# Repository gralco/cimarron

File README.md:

# Cimarron 3D Printer Electronics

## Chipset

Octavo Systems/TI OSD335x

## Other ICs Being Used

Trinamic TMC2130 Stepper Driver

EMMC**G-S100 Embedded MMC

## Operating System

Embedded ARM GNU/Linux Kamikaze

## Bootloader

DAS U-Boot

## Control Software

Potential software to run on Cimarron:

 - [Redeem](https://bitbucket.org/intelligentagent/redeem)
 - [MachineKit](https://github.com/machinekit/machinekit)
 - [Unicorn](https://github.com/fastbot3d/firmware)
 - [Ember-Firmware](https://github.com/spark3dp/ember-firmware)

## Credits

Works that Cimarron is based off of includes:

 - Thing Printer Replicape Rev B3
 - BeagleBone Black Wireless (minus the WL1835 chip)
 - PocketBone
 - BeagleBone Black
 - Tinkerforge Silent Stepper Brick
 - Trinamic TMC-260 Shield

## License

Cimarron is published under [CC-BY-SA 4.0](COPYING.md).

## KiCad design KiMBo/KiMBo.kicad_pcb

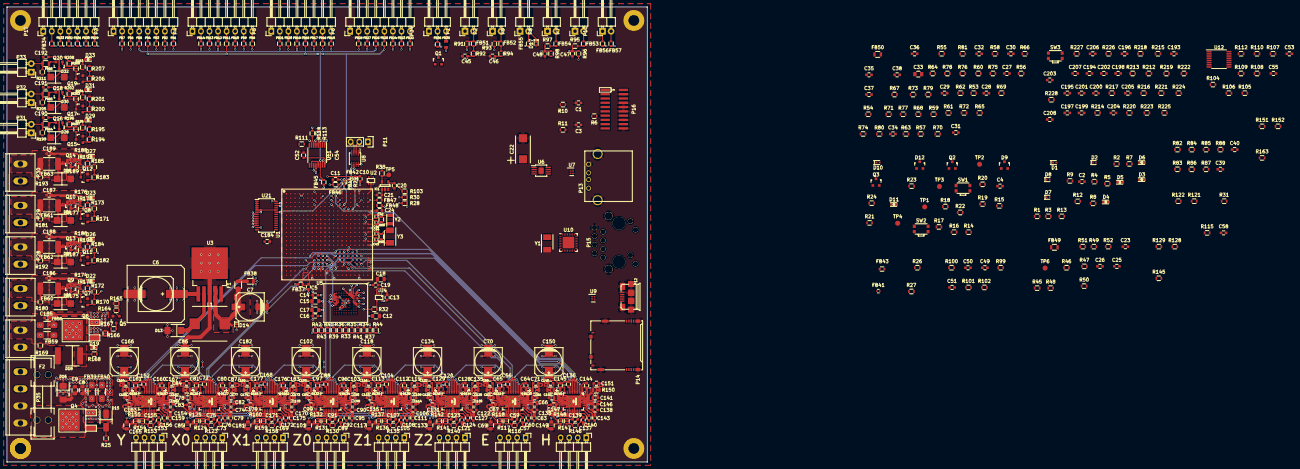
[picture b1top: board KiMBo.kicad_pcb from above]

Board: 6 copper layers, 190.0 x 135.0 mm, 628 parts (0 on the bottom side), 443 nets.

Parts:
C1, C3, C5, C10, C11, C13, C14, C16, C19, C20, C21, C23, C24, C25, C26, C29, C30, C31, C49, C50, C51, C52, C53, C54, C55, C56, C58, C63, C66, C67, C68, C71, C72, C74, C79, C82, C83, C84, C87, C88, C90, C95, C98, C99, C100, C103, C104, C106, C111, C114, C115, C116, C119, C120, C122, C127, C130, C131, C132, C135, C136, C138, C138#2, C143, C146, C147, C148, C151, C152, C154, C159, C162, C163, C164, C167, C168, C170, C175, C178, C179, C180, C183, C184: 100nF; C_0603
C2, C60, C76, C92, C108, C124, C140, C156, C172: 22nF; C_0603
C4: 2.2μF; C_0603
C6: 470μF; c_elec_16x16.5
C7: 220μF; c_elec_8x10.2
C8, C9: 22μF; C_0805
C12, C15, C17: 2.2μF; C_0805
C18: 4.7μF; C_0805
C22: 220μF; TantalC_SizeD_EIA-7343_Reflow
C27, C28: 30pF; C_0603
C32, C61, C62, C64, C65, C77, C78, C80, C81, C93, C94, C96, C97, C109, C110, C112, C113, C125, C126, C128, C129, C141, C142, C144, C145, C157, C158, C160, C161, C173, C174, C176, C177: 470pF; C_0603
C33, C69, C85, C101, C117, C133, C149, C165, C181: 10μF; C_0805
C34: 1μF; C_0603
C35, C36, C37, C38: DNP-15pF; C_0603
C39, C40: 10μF; C_0603
C41, C42, C43, C44: 18pF; Crystal_C_0402
C45, C46, C59, C75, C91, C107, C123, C139, C155, C171: 4.7μF; C_0603
C47, C48: 39nF; C_0603
C57, C73, C89, C105, C121, C137, C153, C169: 470nF; C_0603
C70, C86, C102, C118, C134, C150, C166, C182: 100μF; c_elec_8x10
C185, C186, C187, C188, C189, C190, C191, C192: 4.7nF; C_0603
C193, C194, C195, C196, C197, C198, C199, C200, C201, C202, C203, C204, C205, C206, C207, C208: 47pF; C_0603
D1, D10, D17: TPD1E04U04DPYR; TPD_PX1SON
D2, D7, D8, D14: D5V0F1U2S9; SOD-923
D3, D4, D5, D6, D11, D19, D22, D23, D26, D27, D29, D31, D33: LED; LED_0603
D9: TLVH431; SOT-23
D12: DNP-TLVH431; SOT-23
D13: SK54A-LTP; SK-DO-214AC
D15: SMAZ10; SMA-DO-214AC
D16: SMAJ26A; SK-DO-214AC
D18: SK1545-TP; SK-DO-214AB
D20, D21, D24, D25, D28, D30, D32: MBRA340T3; MBR-DO-214AC
F1: PTC; PTC_SMD0805_Reflow
F2: 0891020.NXS; 3557-2-Fuseholder
FB1, FB2, FB8, FB9, FB15, FB16, FB22, FB23, FB29, FB37: MPZ1608S102ATA00; Ferrite_Bead_0603
FB3, FB4, FB5, FB6, FB7, FB10, FB11, FB12, FB13, FB14, FB17, FB18, FB19, FB20, FB21, FB24, FB25, FB26, FB27, FB28, FB30, FB31, FB32, FB33, FB34, FB36, FB42, FB43, FB45, FB46, FB47, FB48, FB51, FB52, FB53, FB54, FB55, FB56, FB57: MMZ1608A252BTA00; Ferrite_Bead_0603
FB35, FB38: MPZ2012S601AT000; Ferrite_Bead_0805
FB39, FB40, FB58, FB59: BLM31SN500SN1L; R_1206_HandSoldering
FB41, FB44: BLM15AG102SN1D; R_0402
FB49, FB50: LI0805H151R-10; R_0805
FB60, FB61, FB62, FB63: FBMH4532HM132-T; Ferrite_Bead_1812
FB64, FB65, FB66: CIM21J202NE; R_0805
IC1: 24LC32AT-I/OT; SOT-23-5
L1: 47μH; IHLP_Inductor
P1: BED_THERM; Pin_Header_Angled_1x02
P2: ADC; Pin_Header_Angled_1x02
P3: TOOLHEAD0; Pin_Header_Angled_1x08
P4: TOOLHEAD1; Pin_Header_Angled_1x08
P5: DOCK0; Pin_Header_Angled_1x08
P6: DOCK1; Pin_Header_Angled_1x08
P7: X1; Pin_Header_Angled_1x02
P8: Y1; Pin_Header_Angled_1x02
P9: Z1; Pin_Header_Angled_1x02
P10: ENC; Pin_Header_Angled_1x02
P11: Serial; Pin_Header_Straight_1x03
P12: μUSB; USB_MICRO_B_ST-USB-001E
P13: USB_Type_A; USB_A
P14: μSD; SCHA5B0200
P15: Ethernet; Ethernet-LPJ0011BBNL
P16: JTAG
P17: LCD; Pin_Header_Angled_1x07
P18: E_MOTOR; Pin_Header_Angled_1x04
P19: H_MOTOR; Pin_Header_Angled_1x04
P20: X0_MOTOR; Pin_Header_Angled_1x04
P21: X1_MOTOR; Pin_Header_Angled_1x04
P22: Y_MOTOR; Pin_Header_Angled_1x04
P23: Z0_MOTOR; Pin_Header_Angled_1x04
P24: Z1_MOTOR; Pin_Header_Angled_1x04
P25: Z2_MOTOR; Pin_Header_Angled_1x04
P26: BED_HEAT; euro_header_2_angled
P27: E_HEAT; euro_header_2_angled
P28: H_HEAT; euro_header_2_angled
P29: DOCK0_HEAT; euro_header_2_angled
P30: DOCK1_HEAT; euro_header_2_angled
P31: E_FAN; Pin_Header_Angled_1x02
P32: H_FAN; Pin_Header_Angled_1x02
P33: CASE_FAN; Pin_Header_Angled_1x02
P34: PWM; Pin_Header_Angled_1x03
P35: PWR_Input; euro_header_4_angled
Q1, Q5, Q7, Q8, Q11, Q12, Q15, Q17, Q19: 2N7002; SOT-23
Q2: MMBT2907; SOT-23
Q3: DNP-MMBT2907; SOT-23
Q4, Q6: IPD90P03P4-04; TO-252-2Lead
Q9, Q10, Q13, Q14, Q16, Q18, Q20: DMP3098L-7; SOT-23
R1, R2, R3, R4: 1kΩ; R_0603
R5, R8: 470Ω; R_0603
R6, R10, R11, R20, R26, R27, R118, R125, R132, R137, R142, R148, R155, R160: 4.75kΩ; R_0603
R7, R14, R15, R18, R33, R34, R35, R36, R37, R38, R39, R40, R41, R42, R43, R44, R47, R71, R73, R75, R77, R78, R82, R83, R84, R85, R86, R87, R88, R92, R94, R168, R169, R178, R179, R180, R181, R190, R191, R192, R193, R198, R199, R204, R205, R210, R211: 10kΩ; R_0603
R9, R28, R29, R30, R31, R32, R45, R49, R51, R66: 0Ω; R_0603
R12, R13, R91, R93, R96, R98, R100, R101, R102, R103, R104, R105, R106, R107, R108, R109, R110, R111, R112, R113, R114, R115, R121, R122, R128, R129, R145, R151, R152, R163, R165, R166, R167, R172, R173, R174, R175, R176, R177, R184, R185, R186, R187, R188, R189, R195, R196, R197, R201, R202, R203, R207, R208, R209: 4.7kΩ; R_0603
R16: 499Ω; R_0603
R17, R22: DNPΩ; R_0603
R19: 40.2kΩ; R_0603
R21: DNP-499Ω; R_0603
R23: DNP-10kΩ; R_0603
R24: DNP-40.2kΩ; R_0603
R25, R52, R212, R214, R215, R216, R217, R218, R219, R220, R221, R222, R223, R224, R225, R226, R227, R228: 100kΩ; R_0603
R46, R48, R68, R79, R80, R81: 1.5kΩ; R_0603
R50: 100mΩ; R_0603
R53, R164, R170, R171, R182, R183, R194, R200, R206: 10Ω; R_0603
R54, R89: DNP-1MΩ; R_0603
R55: DNP-10Ω; R_0603
R56, R57, R58, R59, R60, R61, R62, R63, R64, R65, R95, R97, R99, R213: 100Ω; R_0603
R67: DNP-0Ω; R_0603
R69, R72, R74, R76: 49.9Ω; R_0603
R70: 12.1kΩ; R_0603
R90: 1MΩ; R_0603
R116, R123, R130, R135, R140, R146, R153, R158: 2.2Ω; R_0603
R117, R124, R131, R136, R141, R147, R154, R159: 5.23kΩ; R_0603
R119, R120, R126, R127, R133, R134, R138, R139, R143, R144, R149, R150, R156, R157, R161, R162: 220mΩ; R_0805
SW1: RESET; KMR_SW_SPST_EVQP7A
SW2: Power; KMR_SW_SPST_EVQP7A
SW3: μSD_Boot; KMR_SW_SPST_EVQP7A
TP1, TP2, TP3, TP4, TP5, TP6: Test_Point; Measurement_Point_Round-SMD-Pad_Small
U1: OSD3358; BGA-400-1-27mm
U2, U4: 74LVC1G06; SC-70-5
U3: LM2592HVSX-5.0; TO-263-5Lead
U5: EMMC**G-S100; EMMCxxG-S100
U6: TPS2051B; DGN-MSOP-8_3x3mm_Pitch0.65mm
U7, U9: TPD4S012; DRY-DFN-6-1EP_2x2mm_Pitch0.5mm
U8: 74LVC2G241; DCT-MSOP-8_3x3mm_Pitch0.65mm
U10: LAN8710A; QFN-32-1EP_5x5mm_Pitch0.5mm
U11, U12: 74HC595; TSSOP-16_4.4x5mm_Pitch0.65mm
U13, U14, U15, U16, U17, U18, U19, U20: TMC2130; QFN36_5X6
U21: PCA9685; TSSOP-28_4.4x9.7mm_Pitch0.65mm
Y1: 7A-25.000MAAJ-T; Crystal_SMD_7A_2Pads
Y2: AH-32.768KDZY-T; Crystal_SMD_32.768kHz_2Pads
Y3: 7A-24.000MAAJ-T; Crystal_SMD_7A_2Pads

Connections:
+24V: C6.1, C8.1, C9.1, C58.2, C63.1, C66.1, C67.1, C69.1, C70.1, C74.2, C79.1, C82.1, C83.1, C85.1, C86.1, C90.2, C95.1, C98.1, C99.1, C101.1, C102.1, C106.2, C111.1, C114.1, C115.1, C117.1, C118.1, C122.2, C127.1, C130.1, C131.1, C133.1, C134.1, C138.2, C138#2.2, C143.1, C146.1, C147.1, C149.1, C150.1, C154.2, C159.1, C162.1, C163.1, C165.1, C166.1, C170.2, C175.1, C178.1, C179.1, C181.1, C182.1, C185.1, C186.1, C187.1, C188.1, C189.1, C190.1, C191.1, C192.1, D16.1, FB39.2, FB40.2, Q6.3, Q9.3, Q10.3, Q13.3, Q14.3, Q16.3, Q18.3, Q20.3, R166.1, R174.1, R176.1, R186.1, R188.1, R196.1, R202.1, R208.1, U3.1, U13.16, U13.30, U13.31, U14.16, U14.30, U14.31, U15.16, U15.30, U15.31, U16.16, U16.30, U16.31, U17.16, U17.30, U17.31, U18.16, U18.30, U18.31, U19.16, U19.30, U19.31, U20.16, U20.30, U20.31
/ADC: C46.2, R94.2, U1.C8
/BED_THERM: C45.2, R92.2, U1.A8
/CLKOUT2: FB44.1, P16.18, R29.1, R163.2, U21.23
/Configuration/LCD.D0.B0--B3: C208.1, R212.1, U1.R1
/Configuration/LCD.D1.B1--B4: C207.1, R214.1, U1.R2
/Configuration/LCD.D2.B2--B5: C206.1, R213.2, R215.2, U1.R3
/Configuration/LCD.D3.B3--B6: C205.1, R216.2, U1.R4
/Configuration/LCD.D4.B4--B7: C204.1, R217.2, U1.T1
/Configuration/LCD.D5.G0--G2: C203.1, R218.2, U1.T2
/Configuration/LCD.D6.G1--G3: C202.1, R219.1, U1.T3
/Configuration/LCD.D7.G2--G4: C201.1, R220.1, U1.T4
/Configuration/LCD.D8.G3--G5: C200.1, R221.1, U1.U1
/Configuration/LCD.D9.G4--G6: C199.1, R222.1, U1.U2
/Configuration/LCD.D10.G5--G7: C198.1, R223.1, U1.U3
/Configuration/LCD.D11.R0--R3: C197.1, R224.1, U1.U4
/Configuration/LCD.D12.R1--R4: C196.1, R225.1, U1.V2
/Configuration/LCD.D13.R2--R5: C195.1, R226.1, U1.V3
/Configuration/LCD.D14.R3--R6: C194.1, R227.2, U1.V4
/Configuration/LCD.D15.R4--R7: C193.1, R228.1, U1.T5
/ENC_A: C50.1, R31.2, R101.1
/ENC_B: C51.1, R102.1, U1.R7
/E_DIR: U1.U13, U13.7
/E_FAULT: R115.2, U1.V12, U13.20
/E_STEP: U1.U18, U13.6
/Endstops/ENC_A_IN: FB56.2, P10.1
/Endstops/ENC_B_IN: FB57.2, P10.2
/Endstops/X1_IN: FB53.2, P7.2
/Endstops/Y1_IN: FB54.2, P8.2
/Endstops/Z1_IN: D17.1, FB55.2, P9.2
/Ethernet/CRS: R65.1, U10.14
/Ethernet/ETH_TXD4: R73.1, U10.18
/Ethernet/GRNA: P15.9, U10.3
/Ethernet/MDIO_CLK: U1.M18, U10.17
/Ethernet/MDIO_DATA: R68.2, U1.M17, U10.16
/Ethernet/MII1_COL: R64.2, U1.H16
/Ethernet/MII1_CRS_DV: R65.2, U1.H17
/Ethernet/MII1_REFCLK: R55.2, R67.2, U1.H18
/Ethernet/MII1_RXCLK: R61.2, U1.L18
/Ethernet/MII1_RXD0: R59.2, U1.M16
/Ethernet/MII1_RXD1: R58.2, U1.L15
/Ethernet/MII1_RXD2: R57.2, U1.L16
/Ethernet/MII1_RXD3: R56.2, U1.L17
/Ethernet/MII1_RXDV: R60.2, U1.J17
/Ethernet/MII1_RXERR: R62.2, U1.J15
/Ethernet/MII1_TXCLK: R63.2, U1.K18
/Ethernet/MII1_TXD0: U1.K17, U10.22
/Ethernet/MII1_TXD1: U1.K16, U10.23
/Ethernet/MII1_TXD2: U1.K15, U10.24
/Ethernet/MII1_TXD3: U1.J18, U10.25
/Ethernet/MII1_TXEN: U1.J16, U10.21
/Ethernet/MODE2: R64.1, R79.2, U10.15
/Ethernet/PHY_VDDCR: C32.1, C34.1, U10.6
/Ethernet/RBIAS: R70.1, U10.32
/Ethernet/RCLKIN: R66.1, R67.1, U10.5
/Ethernet/RD+: C35.1, P15.1, R69.2, U10.31
/Ethernet/RD-: C36.1, P15.2, R72.2, U10.30
/Ethernet/REFCLKO: R55.1, R61.1, R78.1, U10.7
/Ethernet/RXD0/MODE0: R59.1, R81.2, U10.11
/Ethernet/RXD1/MODE1: R58.1, R80.2, U10.10
/Ethernet/RXD2/RMIISEL: R57.1, R77.1, U10.9
/Ethernet/RXD3/PHYAD2: R56.1, R75.1, U10.8
/Ethernet/RXDV: R60.1, U10.26
/Ethernet/RXER/PHYAD0: R62.1, R71.1, U10.13
/Ethernet/TD+: C37.1, P15.3, R74.2, U10.29
/Ethernet/TD-: C38.1, P15.6, R76.2, U10.28
/Ethernet/TXCLK: R63.1, U10.20
/Ethernet/YELA: P15.12, R7.1, U10.2
/Fans/CASE_FAN: C192.2, FB66.2, P33.2, R211.1
/Fans/CASE_FAN_IN: R206.2, R207.2, U21.6
/Fans/E_FAN: C190.2, FB64.2, P31.2, R199.1
/Fans/E_FAN_IN: R194.2, R195.2, U21.8
/Fans/H_FAN: C191.2, FB65.2, P32.2, R205.1
/Fans/H_FAN_IN: R200.2, R201.2, U21.7
/Flash/EMMC_RSTN: R32.1, R44.2, U5.K5
/Flash/GPIO1_16.SIP: R31.1, U1.R13
/Flash/MMC1_CLK: R43.2, U1.U9, U5.M6, U5.M7, U5.N8, U5.P9
/Flash/MMC1_CMD: R42.2, U1.V9, U5.M5, U5.N6, U5.N7, U5.P8
/Flash/MMC1_DAT0: R33.2, U1.U7, U5.A3
/Flash/MMC1_DAT1: R34.2, U1.V7, U5.A4
/Flash/MMC1_DAT2: R35.2, U1.R8, U5.A5
/Flash/MMC1_DAT3: R36.2, U1.T8, U5.A1, U5.B2
/Flash/MMC1_DAT4: R37.2, U1.U8, U5.A2, U5.B3
/Flash/MMC1_DAT5: R39.2, U1.V8, U5.B4, U5.C3, U5.D1, U5.D2
/Flash/MMC1_DAT6: R40.2, U1.R9, U5.B5, U5.C5, U5.D4, U5.E3, U5.F2, U5.G1
/Flash/MMC1_DAT7: R41.2, U1.T9, U5.A8, U5.B6, U5.B7
/H_DIR: U1.V13, U18.7
/H_FAULT: R145.2, U1.T7, U18.20
/H_STEP: U1.R12, U18.6
/Heaters/BED_HEAT: C185.2, FB58.2, FB59.2, P26.1, R169.1
/Heaters/BED_HEAT_IN: R164.2, R165.2, U21.13
/Heaters/DOCK0_HEAT: C187.2, FB61.2, P29.1, R181.1
/Heaters/DOCK0_HEAT_IN: R171.2, R173.2, U21.10
/Heaters/DOCK1_HEAT: C189.2, FB63.2, P30.1, R193.1
/Heaters/DOCK1_HEAT_IN: R183.2, R185.2, U21.9
/Heaters/E_HEAT: C186.2, FB60.2, P27.1, R180.1
/Heaters/E_HEAT_IN: R170.2, R172.2, U21.12
/Heaters/H_HEAT: C188.2, FB62.2, P28.1, R192.1
/Heaters/H_HEAT_IN: R182.2, R184.2, U21.11
/I2C0_SCL: C21.1, FB47.2, IC1.1
/I2C0_SDA: IC1.3, R46.2, U1.C17, U1.C19
/I2C2_SCL: C24.1, FB48.1, U21.26
/I2C2_SDA: U1.D18, U21.27
/JTAG/JTAG_EMU0: P16.13, R6.1, U1.C14
/JTAG/JTAG_EMU1: P16.14, R10.2, U1.B14
/JTAG/JTAG_TD0: P16.7, U1.A11
/JTAG/JTAG_TDI: P16.3, U1.B11
/JTAG/JTAG_TMS: P16.1, U1.C11
/JTAG/~JTAG_TRST: P16.2, R11.1, U1.B10
/MMC0_CLK: P14.5, R88.2, U1.G17
/MMC0_CMD: P14.3, R87.2, U1.G18
/MMC0_DAT0: P14.7, R86.2, U1.G16
/MMC0_DAT1: P14.8, R85.2, U1.G15
/MMC0_DAT2: P14.1, R84.2, U1.F18
/MMC0_DAT3: P14.2, R83.2, U1.F17
/Power/BAT_TEMP: TP2.1, U1.W1
/Power/BAT_VOLT: TP3.1, U1.Y1
/Power/LDO_PGOOD: U1.B5, U1.B20
/Power/PMIC_INT: U1.B18, U1.B19
/Power/PMIC_NWAKEUP: U1.A19, U1.C5
/Power/PMIC_PGOOD: U1.A20, U1.B15, U2.2
/Power/PWR_BUT: SW2.2, SW2.4, U1.D20
/Power/VIN_BAT: TP4.1, U1.Y2, U1.Y3
/SD.CD: P14.10, P16.19, R82.2, U1.C15
/SERVO_0: Q1.2, R12.2, U1.U14
/SIP_I2C0_SCL: FB47.1, R48.2, U1.C16, U1.C20
/SPI0_CS0: FB33.1, U1.A16
/SPI0_MISO: FB31.1, U1.B17
/SPI0_MOSI: FB32.1, FB43.1
/SPI0_SCLK: C10.1, FB30.1, FB42.1
/SPI1_CS0: U1.C12, U11.12, U12.12
/SPI1_CS1: R28.1, R30.1, R103.2, U13.2, U14.2, U15.2, U16.2, U17.2, U18.2, U19.2, U20.2
/SPI1_MISO: FB4.1, FB11.1, FB18.1, FB25.1, U1.B13, U18.5
/SPI1_MOSI: FB5.1, FB12.1, FB19.1, FB26.1, FB45.2, U11.14, U19.4
/SPI1_SCLK: C11.1, FB3.1, FB10.1, FB17.1, FB24.1, FB46.2, U11.11, U12.11, U13.3, U14.3, U15.3, U16.3, U17.3, U18.3, U19.3, U20.3
/Stepper Drivers/E Stepper Driver/5VOUT: C59.1, R116.1, R117.1, U13.25
/Stepper Drivers/E_A1: C64.1, P18.2, U13.34
/Stepper Drivers/E_A2: C61.1, P18.1, U13.32
/Stepper Drivers/E_B1: C65.1, P18.4, U13.13
/Stepper Drivers/E_B2: C62.1, P18.3, U13.15
/Stepper Drivers/E_MISO: U13.5, U18.4
/Stepper Drivers/H Stepper Driver/5VOUT: C139.1, R146.1, R147.1, U18.25
/Stepper Drivers/H_A1: C144.1, P19.2, U18.34
/Stepper Drivers/H_A2: C141.1, P19.1, U18.32
/Stepper Drivers/H_B1: C145.1, P19.4, U18.13
/Stepper Drivers/H_B2: C142.1, P19.3, U18.15
/Stepper Drivers/X0 Stepper Driver/5VOUT: C75.1, R123.1, R124.1, U14.25
/Stepper Drivers/X0_A1: C80.1, P20.2, U14.34
/Stepper Drivers/X0_A2: C77.1, P20.1, U14.32
/Stepper Drivers/X0_B1: C81.1, P20.4, U14.13
/Stepper Drivers/X0_B2: C78.1, P20.3, U14.15
/Stepper Drivers/X0_MISO: U14.5, U20.4
/Stepper Drivers/X1 Stepper Driver/5VOUT: C171.1, R158.1, R159.1, U20.25
/Stepper Drivers/X1_A1: C176.1, P21.2, U20.34
/Stepper Drivers/X1_A2: C173.1, P21.1, U20.32
/Stepper Drivers/X1_B1: C177.1, P21.4, U20.13
/Stepper Drivers/X1_B2: C174.1, P21.3, U20.15
/Stepper Drivers/X1_MISO: U15.4, U20.5
/Stepper Drivers/Y Stepper Driver/5VOUT: C155.1, R153.1, R154.1, U19.25
/Stepper Drivers/Y_A1: C160.1, P22.2, U19.34
/Stepper Drivers/Y_A2: C157.1, P22.1, U19.32
/Stepper Drivers/Y_B1: C161.1, P22.4, U19.13
/Stepper Drivers/Y_B2: C158.1, P22.3, U19.15
/Stepper Drivers/Y_MISO: U14.4, U19.5
/Stepper Drivers/Z0 Stepper Driver/5VOUT: C91.1, R130.1, R131.1, U15.25
/Stepper Drivers/Z0_A1: C96.1, P23.2, U15.34
/Stepper Drivers/Z0_A2: C93.1, P23.1, U15.32
/Stepper Drivers/Z0_B1: C97.1, P23.4, U15.13
/Stepper Drivers/Z0_B2: C94.1, P23.3, U15.15
/Stepper Drivers/Z0_MISO: U15.5, U16.4
/Stepper Drivers/Z1 Stepper Driver/5VOUT: C107.1, R135.1, R136.1, U16.25
/Stepper Drivers/Z1_A1: C112.1, P24.2, U16.34
/Stepper Drivers/Z1_A2: C109.1, P24.1, U16.32
/Stepper Drivers/Z1_B1: C113.1, P24.4, U16.13
/Stepper Drivers/Z1_B2: C110.1, P24.3, U16.15
/Stepper Drivers/Z1_MISO: U16.5, U17.4
/Stepper Drivers/Z2 Stepper Driver/5VOUT: C123.1, R140.1, R141.1, U17.25
/Stepper Drivers/Z2_A1: C128.1, P25.2, U17.34
/Stepper Drivers/Z2_A2: C125.1, P25.1, U17.32
/Stepper Drivers/Z2_B1: C129.1, P25.4, U17.13
/Stepper Drivers/Z2_B2: C126.1, P25.3, U17.15
/Stepper Drivers/Z2_MISO: U13.4, U17.5
/Stepper Drivers/~E_EN: U12.6, U13.22
/Stepper Drivers/~H_EN: U12.7, U18.22
/Stepper Drivers/~X0_EN: U12.15, U14.22
/Stepper Drivers/~X1_EN: U12.1, U20.22
/Stepper Drivers/~Y_EN: U12.2, U19.22
/Stepper Drivers/~Z0_EN: U12.3, U15.22
/Stepper Drivers/~Z1_EN: U12.4, U16.22
/Stepper Drivers/~Z2_EN: U12.5, U17.22
/TCK: P16.9, P16.11, U1.A12
/Thermistors/ADC_IN: FB52.2, P2.2, R93.2
/Thermistors/BED_THERM_IN: FB51.2, P1.2, R91.2
/USB/UART0_RXD: P11.2, R52.1, U8.2
/USB/UART0_RXD_IN: U1.E15, U8.6
/USB/UART0_TXD: P11.3, U8.3
/USB/UART0_TXD_OUT: U1.E16, U8.5
/USB/USB1_DRVVBUS: R47.1, U1.F15, U6.4
/USB/USB1_VBUS: R50.1, U1.T18
/USB/USB.B.VBUS: FB49.2, P13.1
/USB/USB.CLIENT.D+: P12.3, U1.N17, U9.1
/USB/USB.CLIENT.D-: P12.2, U1.N18, U9.2
/USB/USB.CLIENT.ID: P12.4, U1.P16, U9.3
/USB/USB.HOST.D+: P13.3, U1.R17, U7.1
/USB/USB.HOST.D-: P13.2, U1.R18, U7.2
/USB/~UART0_RST: TP6.1, U1.E17
/USR0: R4.2, U1.V15
/USR1: R3.2, U1.U15
/USR2: R2.2, U1.T15
/USR3: R1.2, U1.V16
/X1_ENDSTOP: C47.1, R95.1, R96.1, U1.A14
/X2_ENDSTOP: R121.2, U1.T17, U14.21, U20.21
/XDMA_EVENT_INTRO: FB41.2, P16.17
/X_DIR: U1.V6, U14.7, U20.7
/X_FAULT: R122.2, U1.U6, U14.20, U20.20
/X_STEP: U1.U12, U14.6, U20.6
/Y1_ENDSTOP: C48.1, R97.1, R98.1, U1.V14
/Y2_ENDSTOP: R151.2, U1.T14, U19.21
/Y_DIR: U1.U10, U19.7
/Y_FAULT: R152.2, U1.T6, U19.20
/Y_STEP: U1.T12, U19.6
/Z1_ENDSTOP: C49.1, R99.1, R100.1, U1.U17
/Z2_ENDSTOP: R128.2, U1.C13, U15.21, U16.21, U17.21
/Z_DIR: U1.T11, U15.7, U16.7, U17.7
/Z_FAULT: R129.2, U1.D15, U15.20, U16.20, U17.20
/Z_STEP: U1.T10, U15.6, U16.6, U17.6
/~DISP_INT: FB34.1, U1.T13
/~SR_EN: R104.2, U1.D16, U11.10, U11.13, U12.10
/~SS_DOCK0_NVM: FB21.1, R108.2, U11.3
/~SS_DOCK0_T: FB20.1, R107.2, U11.2
/~SS_DOCK1_NVM: FB28.1, R106.2, U11.1
/~SS_DOCK1_T: FB27.1, R105.2, U11.15
/~SS_E_NVM: FB7.1, R112.2, U11.7
/~SS_E_T: FB6.1, R114.1
/~SS_H_NVM: FB14.1, R110.2, U11.5
/~SS_H_T: FB13.1, R113.1
/~SYS_RESET: C1.1, C4.1, P16.15, R14.2, SW1.2, SW1.4, U1.A10, U2.4, U10.19
/~USB1_OC: R49.2, U1.T16, U6.5
CGND: C1.2, C2.2, C3.2, C4.2, C5.2, C6.2, C7.2, C8.2, C9.2, C10.2, C11.2, C12.2, C13.2, C14.2, C15.2, C16.2, C17.2, C18.2, C19.2, C20.2, C21.2, C22.2, C23.2, C24.2, C25.2, C26.2, C27.2, C28.2, C29.2, C30.2, C31.2, C32.2, C33.2, C34.2, C35.2, C36.2, C37.2, C38.2, C39.2, C40.2, C45.1, C46.1, C47.2, C48.2, C49.2, C50.2, C51.2, C52.2, C53.2, C54.1, C55.2, C56.2, C57.2, C58.1, C59.2, C61.2, C62.2, C64.2, C65.2, C66.2, C67.2, C68.2, C69.2, C70.2, C71.2, C72.2, C73.2, C74.1, C75.2, C77.2, C78.2, C80.2, C81.2, C82.2, C83.2, C84.2, C85.2, C86.2, C87.2, C88.2, C89.2, C90.1, C91.2, C93.2, C94.2, C96.2, C97.2, C98.2, C99.2, C100.2, C101.2, C102.2, C103.2, C104.2, C105.2, C106.1, C107.2, C109.2, C110.2, C112.2, C113.2, C114.2, C115.2, C116.2, C117.2, C118.2, C119.2, C120.2, C121.2, C122.1, C123.2, C125.2, C126.2, C128.2, C129.2, C130.2, C131.2, C132.2, C133.2, C134.2, C135.2, C136.2, C137.2, C138.1, C138#2.1, C139.2, C141.2, C142.2, C144.2, C145.2, C146.2, C147.2, C148.2, C149.2, C150.2, C151.2, C152.2, C153.2, C154.1, C155.2, C157.2, C158.2, C160.2, C161.2, C162.2, C163.2, C164.2, C165.2, C166.2, C167.2, C168.2, C169.2, C170.1, C171.2, C173.2, C174.2, C176.2, C177.2, C178.2, C179.2, C180.2, C181.2, C182.2, C183.2, C184.2, C193.2, C194.2, C195.2, C196.2, C197.2, C198.2, C199.2, C200.2, C201.2, C202.2, C203.2, C204.2, C205.2, C206.2, C207.2, C208.2, D1.2, D2.2, D3.1, D4.1, D5.1, D6.1, D7.2, D8.2, D10.2, D13.2, D14.2, D16.2, D17.2, D18.2, D19.1, D20.2, D21.2, D22.1, D23.1, D24.2, D25.2, D26.1, D27.1, D28.2, D29.1, D30.2, D31.1, D32.2, D33.1, IC1.2, P1.1, P2.1, P3.1, P4.1, P5.1, P6.1, P7.1, P8.1, P9.1, P11.1, P12.5, P12.6, P12.7, P12.8, P12.9, P12.10, P12.11, P13.4, P13.5, P14.6, P14.9, P14.11, P14.12, P14.13, P14.14, P14.15, P14.16, P15.8, P15.13, P15.14, P16.4, P16.8, P16.10, P16.12, P16.16, P16.20, P17.1, P26.2, P27.2, P28.2, P29.2, P30.2, P31.1, P32.1, P33.1, P34.1, P35.3, P35.4, Q5.2, Q7.2, Q8.2, Q11.2, Q12.2, Q15.2, Q17.2, Q19.2, R5.2, R7.2, R8.2, R11.2, R15.2, R20.2, R25.2, R27.2, R45.2, R47.2, R52.2, R70.2, R71.2, R73.2, R75.2, R77.2, R78.2, R118.1, R119.1, R120.1, R125.1, R126.1, R127.1, R132.1, R133.1, R134.1, R137.1, R138.1, R139.1, R142.1, R143.1, R144.1, R148.1, R149.1, R150.1, R155.1, R156.1, R157.1, R160.1, R161.1, R162.1, R165.1, R169.2, R172.1, R173.1, R180.2, R181.2, R184.1, R185.1, R192.2, R193.2, R195.1, R199.2, R201.1, R205.2, R207.1, R211.2, R212.2, R214.2, R219.2, R220.2, R221.2, R222.2, R223.2, R224.2, R225.2, R226.2, R228.2, SW1.1, SW1.3, SW2.1, SW2.3, SW3.2, SW3.4, TP1.1, U1.A1, U1.A18, U1.E19, U1.E20, U1.F8, U1.F19, U1.G8, U1.G9, U1.G11, U1.G12, U1.G19, U1.H6, U1.H7, U1.H8, U1.H9, U1.H10, U1.H12, U1.H19, U1.J6, U1.J7, U1.J8, U1.J9, U1.J10, U1.J11, U1.J19, U1.J20, U1.K7, U1.K9, U1.K10, U1.K11, U1.K19, U1.L10, U1.L11, U1.L12, U1.L13, U1.L19, U1.M6, U1.M7, U1.M8, U1.M9, U1.M10, U1.M12, U1.M14, U1.M19, U1.N7, U1.N10, U1.N11, U1.N14, U1.N19, U1.N20, U1.P19, U1.P20, U1.R19, U1.R20, U1.T19, U1.T20, U1.U19, U1.V1, U1.V18, U1.V19, U1.W2, U1.W3, U1.W5, U1.W6, U1.W7, U1.W8, U1.W9, U1.W10, U1.W11, U1.W12, U1.W13, U1.W14, U1.W15, U1.W16, U1.W17, U1.W18, U1.W19, U1.W20, U1.Y7, U1.Y10, U1.Y12, U1.Y15, U1.Y18, U2.3, U3.3, U3.5, U4.3, U5.C4, U5.D3, U5.E1, U5.E2, U5.E7, U5.G5, U5.H10, U5.K8, U5.N2, U5.N5, U5.P2, U5.P4, U5.P6, U6.1, U6.9, U7.4, U8.1, U8.4, U9.4, U10.33, U11.8, U12.8, U12.13, U13.1, U13.11, U13.12, U13.18, U13.21, U13.24, U13.35, U13.36, U13.37, U14.1, U14.11, U14.12, U14.18, U14.24, U14.35, U14.36, U14.37, U15.1, U15.11, U15.12, U15.18, U15.24, U15.35, U15.36, U15.37, U16.1, U16.11, U16.12, U16.18, U16.24, U16.35, U16.36, U16.37, U17.1, U17.11, U17.12, U17.18, U17.24, U17.35, U17.36, U17.37, U18.1, U18.11, U18.12, U18.18, U18.21, U18.24, U18.35, U18.36, U18.37, U19.1, U19.11, U19.12, U19.18, U19.24, U19.35, U19.36, U19.37, U20.1, U20.11, U20.12, U20.18, U20.24, U20.35, U20.36, U20.37, U21.14
GNDA: U1.A6, U1.A9, U1.E8
unnamed: C2.1, P15.4, P15.5, R9.2
unnamed: C5.1, FB37.1, U1.Y5, U1.Y6
unnamed: C7.1, D14.1, F1.1, L1.2, U3.4
unnamed: C18.1, C19.1, U5.C1, U5.C2
unnamed: C23.1, FB49.1, R50.2, U6.6, U6.7, U6.8, U7.6
unnamed: C27.1, R53.2, Y1.1
unnamed: C28.1, R54.1, R66.2, Y1.2
unnamed: C41.1, R89.1, U1.H20, Y2.2
unnamed: C41.2, C42.2, U1.G20
unnamed: C42.1, R89.2, U1.F20, Y2.1
unnamed: C43.1, R90.1, U1.M20, Y3.2
unnamed: C43.2, C44.2, U1.L20
unnamed: C44.1, R90.2, U1.K20, Y3.1
unnamed: C57.1, R116.2, U13.26
unnamed: C60.1, U13.28
unnamed: C60.2, U13.27
unnamed: C63.2, U13.29
unnamed: C68.1, R119.2, U13.14
unnamed: C71.1, R120.2, U13.33
unnamed: C73.1, R123.2, U14.26
unnamed: C76.1, U14.28
unnamed: C76.2, U14.27
unnamed: C79.2, U14.29
unnamed: C84.1, R126.2, U14.14
unnamed: C87.1, R127.2, U14.33
unnamed: C89.1, R130.2, U15.26
unnamed: C92.1, U15.28
unnamed: C92.2, U15.27
unnamed: C95.2, U15.29
unnamed: C100.1, R133.2, U15.14
unnamed: C103.1, R134.2, U15.33
unnamed: C105.1, R135.2, U16.26
unnamed: C108.1, U16.28
unnamed: C108.2, U16.27
unnamed: C111.2, U16.29
unnamed: C116.1, R138.2, U16.14
unnamed: C119.1, R139.2, U16.33
unnamed: C121.1, R140.2, U17.26
unnamed: C124.1, U17.28
unnamed: C124.2, U17.27
unnamed: C127.2, U17.29
unnamed: C132.1, R143.2, U17.14
unnamed: C135.1, R144.2, U17.33
unnamed: C137.1, R146.2, U18.26
unnamed: C140.1, U18.28
unnamed: C140.2, U18.27
unnamed: C143.2, U18.29
unnamed: C148.1, R149.2, U18.14
unnamed: C151.1, R150.2, U18.33
unnamed: C153.1, R153.2, U19.26
unnamed: C156.1, U19.28
unnamed: C156.2, U19.27
unnamed: C159.2, U19.29
unnamed: C164.1, R156.2, U19.14
unnamed: C167.1, R157.2, U19.33
unnamed: C169.1, R158.2, U20.26
unnamed: C172.1, U20.28
unnamed: C172.2, U20.27
unnamed: C175.2, U20.29
unnamed: C180.1, R161.2, U20.14
unnamed: C183.1, R162.2, U20.33
unnamed: D3.2, R1.1
unnamed: D4.2, R2.1
unnamed: D5.2, R3.1
unnamed: D6.2, R4.1
unnamed: D7.1, FB36.1, Q1.3, R13.2
unnamed: D9.1, Q2.1, R16.2, R17.2
unnamed: D9.3, R17.1, R18.2, R19.1
unnamed: D11.1, R20.1
unnamed: D12.1, Q3.1, R21.2, R22.2
unnamed: D12.3, R22.1, R23.2, R24.1
unnamed: D13.1, L1.1, U3.2
unnamed: D15.1, FB39.1, FB40.1, Q4.3
unnamed: D15.2, Q4.1, R25.1
unnamed: D18.1, FB58.1, FB59.1, Q6.2, R168.1
unnamed: D19.2, R168.2
unnamed: D20.1, FB60.1, Q9.2, R178.1
unnamed: D21.1, FB61.1, Q10.2, R179.1
unnamed: D22.2, R178.2
unnamed: D23.2, R179.2
unnamed: D24.1, FB62.1, Q13.2, R190.1
unnamed: D25.1, FB63.1, Q14.2, R191.1
unnamed: D26.2, R190.2
unnamed: D27.2, R191.2
unnamed: D28.1, FB64.1, Q16.2, R198.1
unnamed: D29.2, R198.2
unnamed: D30.1, FB65.1, Q18.2, R204.1
unnamed: D31.2, R204.2
unnamed: D32.1, FB66.1, Q20.2, R210.1
unnamed: D33.2, R210.2
unnamed: F1.2, FB38.1
unnamed: F2.1, P35.1, P35.2
unnamed: F2.2, Q4.2
unnamed: FB1.2, P3.8
unnamed: FB2.2, P3.7
unnamed: FB3.2, P3.6
unnamed: FB4.2, P3.5
unnamed: FB5.2, P3.4
unnamed: FB6.2, P3.3
unnamed: FB7.2, P3.2
unnamed: FB8.2, P4.8
unnamed: FB9.2, P4.7
unnamed: FB10.2, P4.6
unnamed: FB11.2, P4.5
unnamed: FB12.2, P4.4
unnamed: FB13.2, P4.3
unnamed: FB14.2, P4.2
unnamed: FB15.2, P5.8
unnamed: FB16.2, P5.7
unnamed: FB17.2, P5.6
unnamed: FB18.2, P5.5
unnamed: FB19.2, P5.4
unnamed: FB20.2, P5.3
unnamed: FB21.2, P5.2
unnamed: FB22.2, P6.8
unnamed: FB23.2, P6.7
unnamed: FB24.2, P6.6
unnamed: FB25.2, P6.5
unnamed: FB26.2, P6.4
unnamed: FB27.2, P6.3
unnamed: FB28.2, P6.2
unnamed: FB29.2, P17.7
unnamed: FB30.2, P17.6
unnamed: FB31.2, P17.5
unnamed: FB32.2, P17.4
unnamed: FB33.2, P17.3
unnamed: FB34.2, P17.2
unnamed: FB35.2, P34.3
unnamed: FB36.2, P34.2
unnamed: FB41.1, U1.A15
unnamed: FB42.2, U1.A17
unnamed: FB43.2, U1.B16
unnamed: FB44.2, U1.D14
unnamed: FB45.1, U1.D12
unnamed: FB46.1, U1.A13
unnamed: FB48.2, U1.D17
unnamed: FB51.1, R92.1
unnamed: FB52.1, R94.1
unnamed: FB53.1, R95.2
unnamed: FB54.1, R97.2
unnamed: FB55.1, R99.2
unnamed: FB56.1, R101.2
unnamed: FB57.1, R102.2
unnamed: IC1.5, R38.1, TP5.1
unnamed: P15.10, R5.1
unnamed: P15.11, R8.1
unnamed: Q5.1, R164.1
unnamed: Q5.3, R167.2
unnamed: Q6.1, R166.2, R167.1
unnamed: Q7.1, R170.1
unnamed: Q7.3, R175.2
unnamed: Q8.1, R171.1
unnamed: Q8.3, R177.2
unnamed: Q9.1, R174.2, R175.1
unnamed: Q10.1, R176.2, R177.1
unnamed: Q11.1, R182.1
unnamed: Q11.3, R187.2
unnamed: Q12.1, R183.1
unnamed: Q12.3, R189.2
unnamed: Q13.1, R186.2, R187.1
unnamed: Q14.1, R188.2, R189.1
unnamed: Q15.1, R194.1
unnamed: Q15.3, R197.2
unnamed: Q16.1, R196.2, R197.1
unnamed: Q17.1, R200.1
unnamed: Q17.3, R203.2
unnamed: Q18.1, R202.2, R203.1
unnamed: Q19.1, R206.1
unnamed: Q19.3, R209.2
unnamed: Q20.1, R208.2, R209.1
unnamed: R15.1, U1.B4
unnamed: R26.2, R27.1, U1.C9
unnamed: R28.2, U1.C18
unnamed: R29.2, U1.D13
unnamed: R30.2, U1.B12
unnamed: R32.2, U4.4
unnamed: R45.1, U1.P17
unnamed: R51.2, U1.P15
unnamed: R53.1, R54.2, U10.4
unnamed: R109.2, R113.2, U11.4
unnamed: R111.2, R114.2, U11.6
unnamed: R117.2, R118.2, U13.23
unnamed: R124.2, R125.2, U14.23
unnamed: R131.2, R132.2, U15.23
unnamed: R136.2, R137.2, U16.23
unnamed: R141.2, R142.2, U17.23
unnamed: R147.2, R148.2, U18.23
unnamed: R154.2, R155.2, U19.23
unnamed: R159.2, R160.2, U20.23
unnamed: R213.1, SW3.1, SW3.3
unnamed: U1.C6, U1.D19
unnamed: U1.R14, U4.2
unnamed: U11.9, U12.14
unnamed: U21.1, U21.2, U21.3, U21.4, U21.5, U21.24
SYS_5V: C22.1, U1.W4, U1.Y4, U6.2, U6.3
USB_DC: C25.1, P12.1, R51.1, U1.Y8, U1.Y9, U9.6
VCC: C3.1, C12.1, C13.1, C14.1, C15.1, C16.1, C17.1, C20.1, C26.1, C29.1, C39.1, C40.1, C52.1, C53.1, C54.2, C55.1, C56.1, C72.1, C88.1, C104.1, C120.1, C136.1, C152.1, C168.1, C184.1, D1.1, D10.1, FB2.1, FB9.1, FB16.1, FB23.1, FB50.1, IC1.4, P14.4, P16.5, Q1.1, Q3.3, R6.2, R10.1, R12.1, R14.1, R21.1, R23.1, R26.1, R33.1, R34.1, R35.1, R36.1, R37.1, R38.2, R39.1, R40.1, R41.1, R42.1, R43.1, R44.1, R46.1, R48.1, R49.1, R68.1, R79.1, R80.1, R81.1, R82.1, R83.1, R84.1, R85.1, R86.1, R87.1, R88.1, R96.2, R98.2, R100.2, R103.1, R104.1, R105.1, R106.1, R107.1, R108.1, R109.1, R110.1, R111.1, R112.1, R115.1, R121.1, R122.1, R128.1, R129.1, R145.1, R151.1, R152.1, R163.1, R215.1, R216.1, R217.1, R218.1, R227.1, U1.U20, U1.V20, U4.5, U5.A9, U5.B8, U5.C6, U5.C7, U5.E6, U5.F5, U5.J10, U5.K9, U5.M4, U5.N4, U5.P3, U5.P5, U8.7, U8.8, U10.12, U11.16, U12.16, U13.8, U14.8, U15.8, U16.8, U17.8, U18.8, U19.8, U20.8, U21.28
VDD_1V8: D9.2, D12.2, Q2.2, Q3.2, R19.2, R24.2, U1.D10, U1.E9, U1.N16, U1.R16, U2.5
VDD_3V3A: Q2.3, R16.1, R18.1, U1.N5, U1.P5, U1.P6, U1.P7
VDD_3V3AUX: D11.2, U1.Y11
VDD_5V: D2.1, D8.1, FB1.1, FB8.1, FB15.1, FB22.1, FB29.1, FB35.1, FB37.2, FB38.2, R13.1
VDD_ADC: R91.1, R93.1, U1.A4, U1.A5, U1.B9, U1.D8
VDD_PHYA: C30.1, C31.1, C33.1, FB50.2, R9.1, R69.1, R72.1, R74.1, R76.1, U10.1, U10.27

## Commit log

2016-11-04 Another README update
2016-11-04 Fix license link in README
2016-11-04 Another try at fixing the link
2016-11-04 Another attempt
2016-11-04 Yet another README update
2016-11-17 Update to use OSD335x as the main chipset
2016-11-21 Move various symbols, add notes, add labels
2016-12-08 Add comparison spreadsheet
    Contains comparison of FW, MCUs, and Wifi chips
2016-12-08 Update the schematic with various nets and labels
2016-12-09 More updates to the schematics
2017-02-02 Add eMMC to the schematic
2017-02-02 Add 153-Pin BGA eMMC footprint
2017-02-02 Update schematic module file names, add HDMI module and SD module
2017-02-06 More progress made on the HDMI module
2017-02-09 Use the TMC2130 stepper driver, document and calculate the stepper motor current
    The current to the motors are set by IRUN and IHOLD of the IHOLD_IRUN register
2017-02-10 Update fixed reference voltage resistor values
2017-02-10 Update the stepper schematics' passive components
2017-02-14 Update the fixed Vain voltage and begin placing connectors at the highest level (root) of the hierarchical sheet structure
2017-02-15 Bring more interfaces out to the root sheet and begin connecting modules
2017-02-16 Create nodes for more SS, add H stepper, begin fixing power rail names
2017-02-17 Update the rest of the power rails and add two more stepper drivers
    Now has *nine* stepper drivers, this will increase cost, and may drastically increase development time...
2017-02-20 Use only one driver on Y, NAND X and Z FAULT and SG signals
    Dual X carriage will need to be tested to determine if two seperate drivers are required for X
2017-02-22 Show which components are DNP, begin spec of components, and refine the power input circuit
2017-02-27 Add low pass filters to the outputs going to the heaters, fans, and to the endstop inputs.
    The values of the passives need to be tweaked.
    Ferrites need to be placed in series with the output to the heaters and fans.
2017-02-28 Add more low-pass filters to the outputs, add reverse polarity protection
2017-03-01 Update ferrite values, select fuse based on interrupt rating
    The PSU needs to be able to supply at LEAST 25A to blow the fuse
2017-03-02 Move EN and SS lines, update 5V regulator passive values
2017-03-03 Annotate all components, now passing ERC, added ferrites to the rest of the connectors
2017-03-06 Clean up various parts of the schematic, high level sheet has annoated modules
2017-03-07 Reorder the SS and EN lines from the shift registers such that the previously enabled/disabled motors stay enabled/disabled whilst writting to the shift register
    Change 10k resistors to 4.7k, flip the open-drain inverter connected to B15 (PMTC_PGOOD)
    Update the links in the README
    Update the PDF schematic
2017-03-09 Begin entry of component values
2017-03-10 Entry of additional component values
2017-03-13 Replace most electrolytic cap symbols symbols with the standard, non-polarized (ceramic) cap symbol
2017-03-14 Rename connectors to their respective functionality
2017-03-14 Update README to point to new location of COPYING.md
    Make the Unicorn firmware a hyperlink
2017-03-17 Associate more footprints
2017-03-24 Add equivalent annotations document, associate more footprints
2017-03-28 Change the endstop RC filter
    Lower the time constant
    Reduce the series resistor to 100Ohms
2017-03-29 Connect X and Z stepper driver open-drain DIAG0 and DIAG1 lines together
2017-04-14 Leave SPI0 free for a display, reassign pins so SPI1 is available
    Fix some typos/errors
2017-04-18 Use fixed 5V LM2592HV Buck, include SPI0 header for LCD
2017-04-18 Assocate more footprints
2017-04-19 More footprint association
2017-04-21 Create more footprints and add more associations
2017-04-21 Add more footprints and more associations, one association left!
2017-04-24 Complete footprint association
    Next step is layout, adjustments may need to be made to the schematic at a later point.
2017-04-24 Generate netlist
2017-04-24 Fix footprints and associations before exporting/importing the netlist
2017-04-24 Import the netlist
2017-04-24 Begin layout
    Arrange all connectors to get a feel for the area.
2017-04-24 Arrange connectors and E-stepper circuit
2017-04-25 More progress on the stepper driver layout
2017-04-26 Tune in the stepper motor circuit, prior to removing HDMI
2017-04-26 Remove HDMI from the schematic
2017-04-26 Read in the new netlist, HDMI removed from the layout
2017-04-27 More stepper motor driver progress
2017-04-28 Duplicate the stepper circuit, remove extra Y connector
    The Y motors will be wired in series through the motor connectors on the machine
2017-05-01 Change associated annotations of X0, X1, Y, and Z0 stepper circuits' components
2017-05-02 Complete stepper footprint association, move silkscreen, start DC fuse, polarity protection, and circuit
2017-05-03 Begin laying out the bed heater circuit
2017-05-05 Expose the pad under the tmc2130 stepper drivers
2017-05-08 Add F1 PTC resettable fuse at the 5V output, begin E's heater circuit layout
2017-05-09 Daisy chain the SPI stepper motor driver interface, continue work on the E-heater layout
2017-05-10 Continue buck converter layout
2017-05-12 Route 24V to the buck, add PTC fuse to 5V output
2017-05-17 Add ferrite beads to the 5V and 3V pins at the SPI connectors
2017-05-17 Update the pdf schematic after adding additional ferrite beads
2017-05-18 Fit bottom left mounting hole, begin fan circuit layout
2017-05-19 Complete the 24V fan circuit layout, beginning SPI header layout
2017-05-22 Complete SPI, ADC, and Endstop header layout/position, add zone around the SiP
2017-05-23 Set up design rules for the eMMC chip, begin BGA placement and routing
2017-05-24 Begin laying out the crystal circuit for the osd335x
2017-05-25 Remove the unneeded oscillator, track down which components are underneath the OSD3358 and put them on the top
2017-05-26 Move ICs and connector interfaces in place, fix incorrect net for C12, and C14-C17, ready to route the eMMC traces
2017-05-31 Routing data lines between OSD335x and the eMMC chip
2017-06-01 Complete parallel data bus routing from the eMMC to the CPU
    Center the SiP on the PCB
    Add LPFs at the I2Cs' SCL outputs
2017-06-02 Routing open-drain output inverters, SOT-5 I2C EEPROM, begin adding bypass caps around the eMMC
2017-06-05 Route power to CPU, complete eMMC routing
2017-06-08 Route the PCA9685 PWM lines, route more SCLK traces
2017-06-09 Route SCLK, MISO, and MOSI to each slave
2017-06-14 Use only one pull up resistor on the stepper motor driver DIAG pins, use the TMC2130's freewheel register functionality instead of driving the enable line via a shift register, begin routing step, di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
2017-06-15 Route VDD_5V and VCC to printer-related headers, begin routing endstops
2017-07-31 Update pdf of schematic
2017-07-31 Update readme to use github's markup
2017-07-31 Use rescued crystal and LED schematic symbols
